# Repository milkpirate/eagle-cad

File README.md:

# eagle-cad
For this PCB development Eagle CAD v6.1.0 was heavily used. Could also contain code snippets.

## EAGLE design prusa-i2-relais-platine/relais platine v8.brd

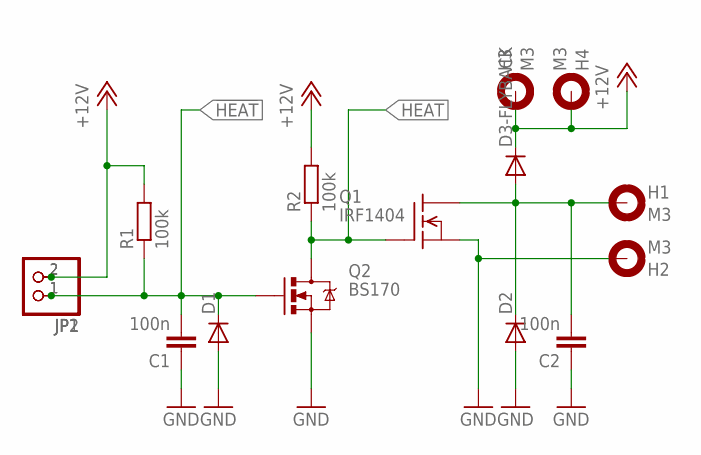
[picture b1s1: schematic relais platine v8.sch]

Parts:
C1, C2: 100n; C0805K
D1, D2, D3-FLYBACK: DIODE-MINIMELF; MINIMELF
H1, H2, H3, H4: M3; 3,0-PAD
JP1: PINHD-1X2; 1X02
JP2: PINHD-1X2/90; 1X02/90
Q1: IRF1404; TO220
Q2: BS170; SOT23-3
R1, R2: 100k; M0805

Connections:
!HEAT: C1.2, D1.C, JP1.1, JP2.1, Q2.1 (G), R1.1
+12V: D3-FLYBACK.C, H3.B3,0, H4.B3,0, JP1.2, JP2.2, R1.2, R2.2
GND: C1.1, C2.1, D1.A, D2.A, H2.B3,0, Q1.3 (S), Q2.2 (S)
HEAT: Q1.1 (G), Q2.3 (D), R2.1
HIGH: C2.2, D2.C, D3-FLYBACK.A, H1.B3,0, Q1.2 (D)

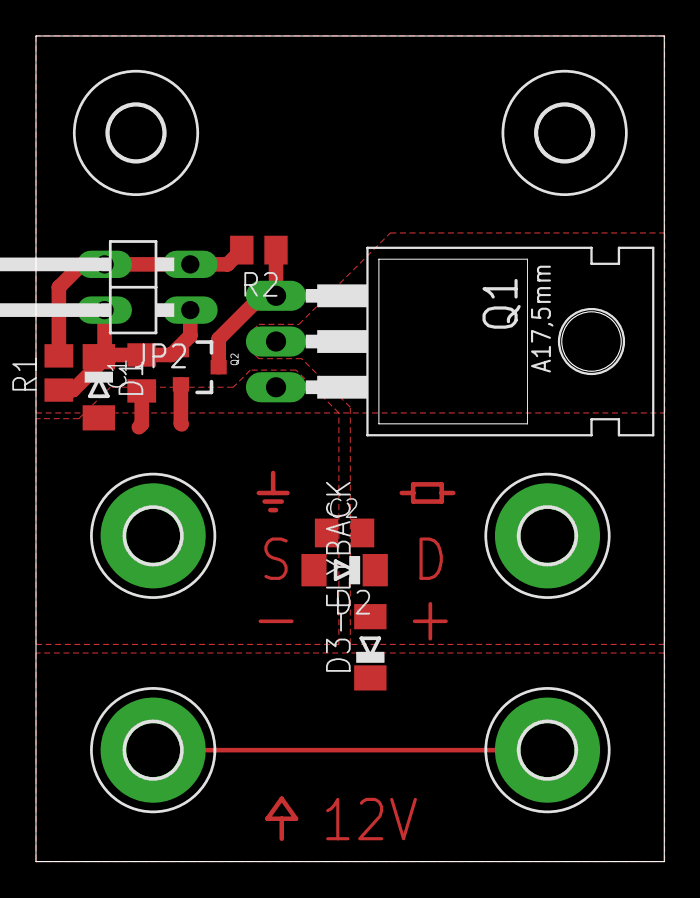
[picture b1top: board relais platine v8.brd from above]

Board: 2 copper layers, 34.9 x 45.9 mm, 17 parts (1 on the bottom side), 5 nets.

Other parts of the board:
U$1, U$2: 3,0

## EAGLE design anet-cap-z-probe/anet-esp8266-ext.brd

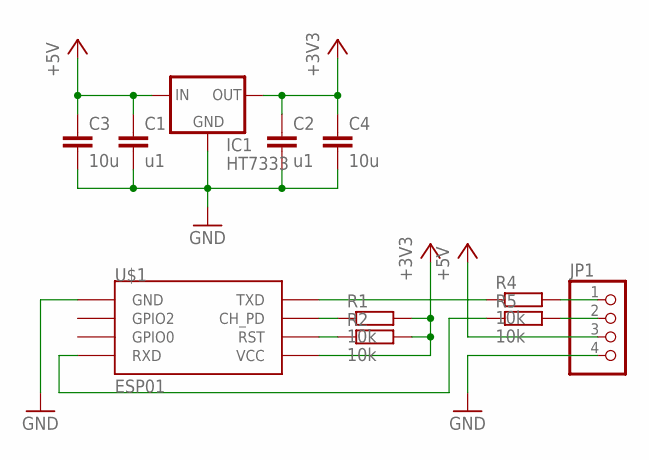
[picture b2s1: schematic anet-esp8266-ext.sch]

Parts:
C1: u1; C0805
C2: u1; C0805K
C3, C4: 10u; C0805K
IC1: HT7333; SOT-89
JP1: PINHD-1X4; 1X04
R1, R2, R5: 10k; M0805
R4: 10k; R0805
U$1: ESP01

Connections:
+3V3: C2.1, C4.1, IC1.1 (OUT), R1.2, R2.2, U$1.VCC
+5V: C1.1, C3.1, IC1.3 (IN), IC1.4 (IN), JP1.3
GND: C1.2, C2.2, C3.2, C4.2, IC1.2 (GND), JP1.4, U$1.GND
unnamed: R1.1, U$1.CH_PD
unnamed: JP1.1, R4.2
unnamed: JP1.2, R5.2
unnamed: R2.1, U$1.RST
RX: R5.1, U$1.RX (RXD)
TX: R4.1, U$1.TX (TXD)

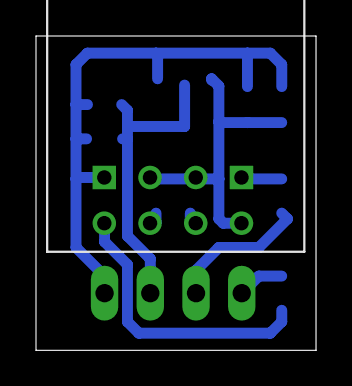
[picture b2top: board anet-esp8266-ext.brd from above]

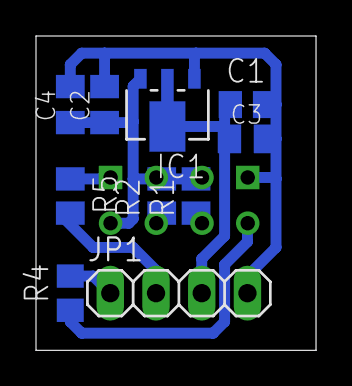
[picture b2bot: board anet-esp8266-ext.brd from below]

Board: 2 copper layers, 15.6 x 17.5 mm, 11 parts (10 on the bottom side), 9 nets.

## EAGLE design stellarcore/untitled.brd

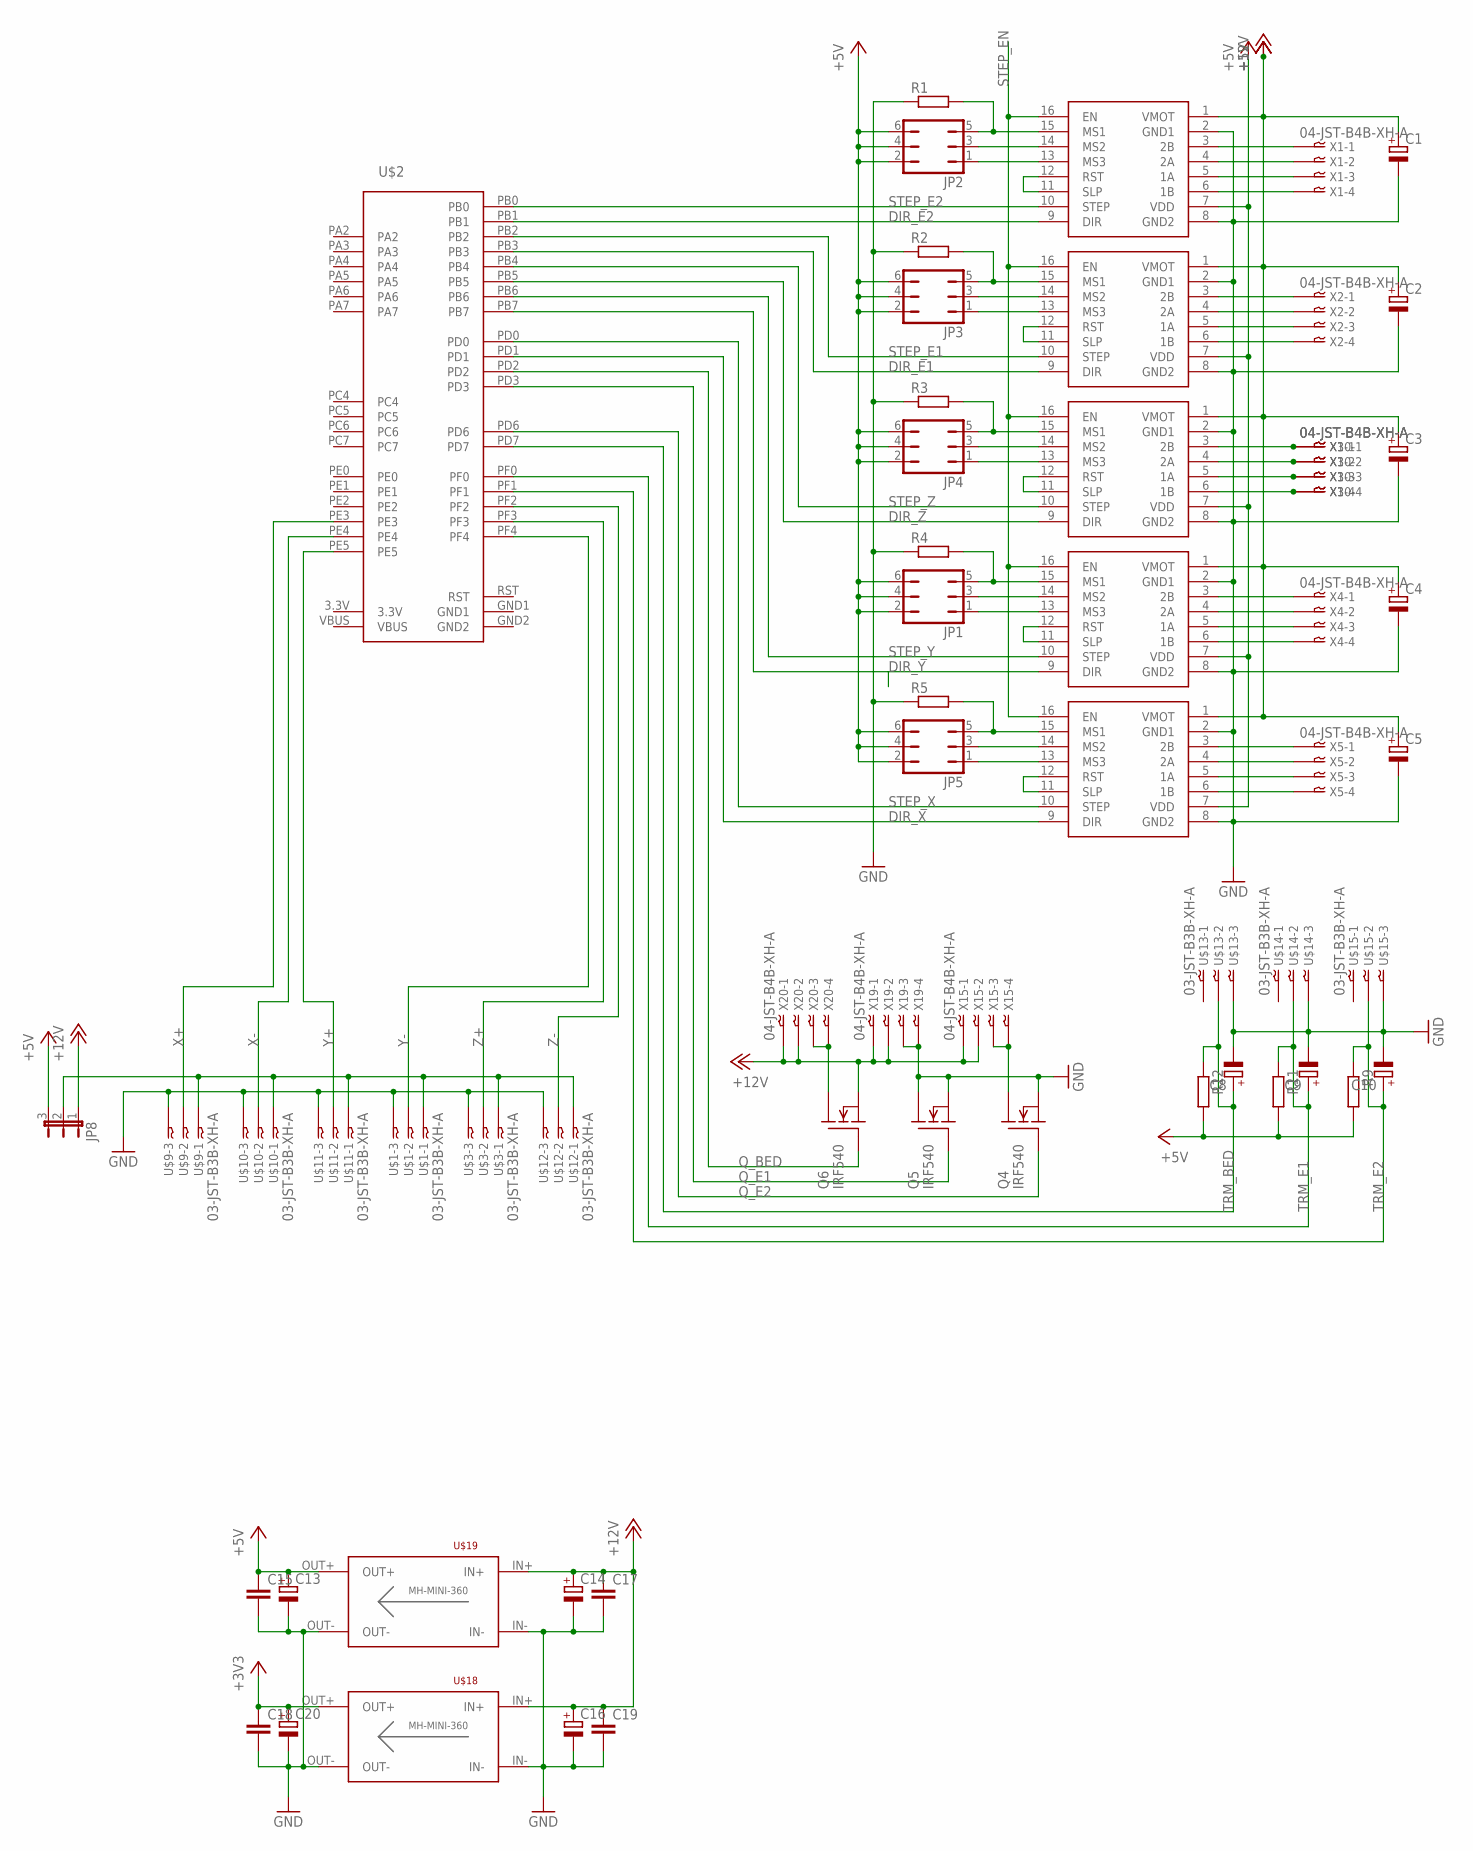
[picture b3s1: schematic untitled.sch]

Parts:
C1, C2, C3, C4, C5: CPOL-EUE2.5-7; E2,5-7
C8, C9, C10, C13, C14, C16, C20: CPOL-EUE2.5-5; E2,5-5
C15, C17, C18, C19: C-EU025-025X050; C025-025X050
JP1, JP2, JP3, JP4, JP5: JP3Q
JP8: JP2E; JP2
Q4, Q5, Q6: IRF540; TO220
R1, R2, R3, R4, R5, R9, R11, R12: R-EU_0204/7; 0204/7
U$1, U$3, U$9, U$10, U$11, U$12, U$13, U$14, U$15: 03-JST-B3B-XH-A; B3B-XH
U$2: STELLARIS-LAUNCHPADSTELLARIS-LAUNCHPAD; LAUNCHPAD-XL
U$4, U$5, U$6, U$7, U$8: POLOLUESTEPPERDRIVER; DIL16
U$18, U$19: DC-DC_CONV_MINISTD; DC-DC_CONV_MINI
X1, X2, X3, X4, X5, X10, X15, X19, X20: 04-JST-B4B-XH-A; B4B-XH

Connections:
3.3V: U$2.3.3V
+3V3: C18.1, C20.+, U$18.OUT+
+5V: C13.+, C15.1, JP1.2, JP1.4, JP1.6, JP2.2, JP2.4, JP2.6, JP3.2, JP3.4, JP3.6, JP4.2, JP4.4, JP4.6, JP5.2, JP5.4, JP5.6, JP8.3, R9.2, R11.2, R12.2, U$4.7 (VDD), U$5.7 (VDD), U$6.7 (VDD), U$7.7 (VDD), U$8.7 (VDD), U$19.OUT+
+12V: C1.+, C2.+, C3.+, C4.+, C5.+, C14.+, C16.+, C17.1, C19.1, JP8.1, Q6.3 (S), U$4.1 (VMOT), U$5.1 (VMOT), U$6.1 (VMOT), U$7.1 (VMOT), U$8.1 (VMOT), U$18.IN+, U$19.IN+, X15.P$1, X15.P$2, X19.P$1, X19.P$2, X20.P$1, X20.P$2
DIR_E1: U$2.PB3, U$7.9 (DIR)
DIR_E2: U$2.PB1, U$8.9 (DIR)
DIR_X: U$2.PD1, U$4.9 (DIR)
DIR_Y: U$5.9 (DIR)
DIR_Z: U$2.PB5, U$6.9 (DIR)
GND: C1.-, C2.-, C3.-, C4.-, C5.-, C8.-, C9.-, C10.-, C13.-, C14.-, C15.2, C16.-, C17.2, C18.2, C19.2, C20.-, Q4.3 (S), Q5.2 (D), Q5.3 (S), R1.1, R2.1, R3.1, R4.1, R5.1, U$1.P$3, U$3.P$3, U$4.2 (GND1), U$4.8 (GND2), U$5.2 (GND1), U$5.8 (GND2), U$6.2 (GND1), U$6.8 (GND2), U$7.2 (GND1), U$7.8 (GND2), U$8.2 (GND1), U$8.8 (GND2), U$9.P$3, U$10.P$3, U$11.P$3, U$12.P$3, U$13.P$3, U$14.P$3, U$15.P$3, U$18.IN-, U$18.OUT-, U$19.IN-, U$19.OUT-, X19.P$3, X19.P$4
GND2: U$2.GND2
unnamed: JP1.1, U$5.13 (MS3)
unnamed: JP1.3, U$5.14 (MS2)
unnamed: JP1.5, R4.2, U$5.15 (MS1)
unnamed: U$8.11 (SLP), U$8.12 (RST)
unnamed: U$7.11 (SLP), U$7.12 (RST)
unnamed: U$6.11 (SLP), U$6.12 (RST)
unnamed: U$5.11 (SLP), U$5.12 (RST)
unnamed: U$4.11 (SLP), U$4.12 (RST)
unnamed: JP2.1, U$8.13 (MS3)
unnamed: JP2.3, U$8.14 (MS2)
unnamed: JP2.5, R1.2, U$8.15 (MS1)
unnamed: JP3.1, U$7.13 (MS3)
unnamed: JP3.3, U$7.14 (MS2)
unnamed: JP3.5, R2.2, U$7.15 (MS1)
unnamed: JP4.1, U$6.13 (MS3)
unnamed: JP4.3, U$6.14 (MS2)
unnamed: JP4.5, R3.2, U$6.15 (MS1)
unnamed: JP5.1, U$4.13 (MS3)
unnamed: JP5.3, U$4.14 (MS2)
unnamed: JP5.5, R5.2, U$4.15 (MS1)
unnamed: U$8.3 (2B), X1.P$1
unnamed: U$8.4 (2A), X1.P$2
unnamed: U$8.5 (1A), X1.P$3
unnamed: U$8.6 (1B), X1.P$4
unnamed: U$7.3 (2B), X2.P$1
unnamed: U$7.4 (2A), X2.P$2
unnamed: U$7.5 (1A), X2.P$3
unnamed: U$7.6 (1B), X2.P$4
unnamed: U$6.3 (2B), X3.P$1, X10.P$1
unnamed: U$6.4 (2A), X3.P$2, X10.P$2
unnamed: U$6.5 (1A), X3.P$3, X10.P$3
unnamed: U$6.6 (1B), X3.P$4, X10.P$4
unnamed: U$5.3 (2B), X4.P$1
unnamed: U$5.4 (2A), X4.P$2
unnamed: U$5.5 (1A), X4.P$3
unnamed: U$5.6 (1B), X4.P$4
unnamed: U$4.3 (2B), X5.P$1
unnamed: U$4.4 (2A), X5.P$2
unnamed: U$4.5 (1A), X5.P$3
unnamed: U$4.6 (1B), X5.P$4
unnamed: JP8.2, U$1.P$1, U$3.P$1, U$9.P$1, U$10.P$1, U$11.P$1, U$12.P$1
unnamed: Q4.2 (D), X15.P$3, X15.P$4
unnamed: Q6.2 (D), X20.P$3, X20.P$4
Q_BED: Q6.1 (G), U$2.PD2
Q_E1: Q5.1 (G), U$2.PD3
Q_E2: Q4.1 (G), U$2.PD6
RST: U$2.RST
STEP_E1: U$2.PB2, U$7.10 (STEP)
STEP_E2: U$2.PB0, U$8.10 (STEP)
STEP_EN: U$4.16 (EN), U$5.16 (EN), U$6.16 (EN), U$7.16 (EN), U$8.16 (EN)
STEP_X: U$2.PD0, U$4.10 (STEP)
STEP_Y: U$2.PB6, U$5.10 (STEP)
STEP_Z: U$2.PB4, U$6.10 (STEP)
TRM_BED: C8.+, R12.1, U$2.PD7, U$13.P$2
TRM_E1: C9.+, R11.1, U$2.PF0, U$14.P$2
TRM_E2: C10.+, R9.1, U$2.PF1, U$15.P$2
VBUS: U$2.VBUS
X+: U$2.PE3, U$9.P$2
X-: U$2.PE4, U$10.P$2
Y+: U$2.PE5, U$11.P$2
Y-: U$1.P$2, U$2.PF4
Z+: U$2.PF3, U$3.P$2
Z-: U$2.PF2, U$12.P$2

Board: 2 copper layers, 59 parts (0 on the bottom side), 69 nets, no tracks yet.

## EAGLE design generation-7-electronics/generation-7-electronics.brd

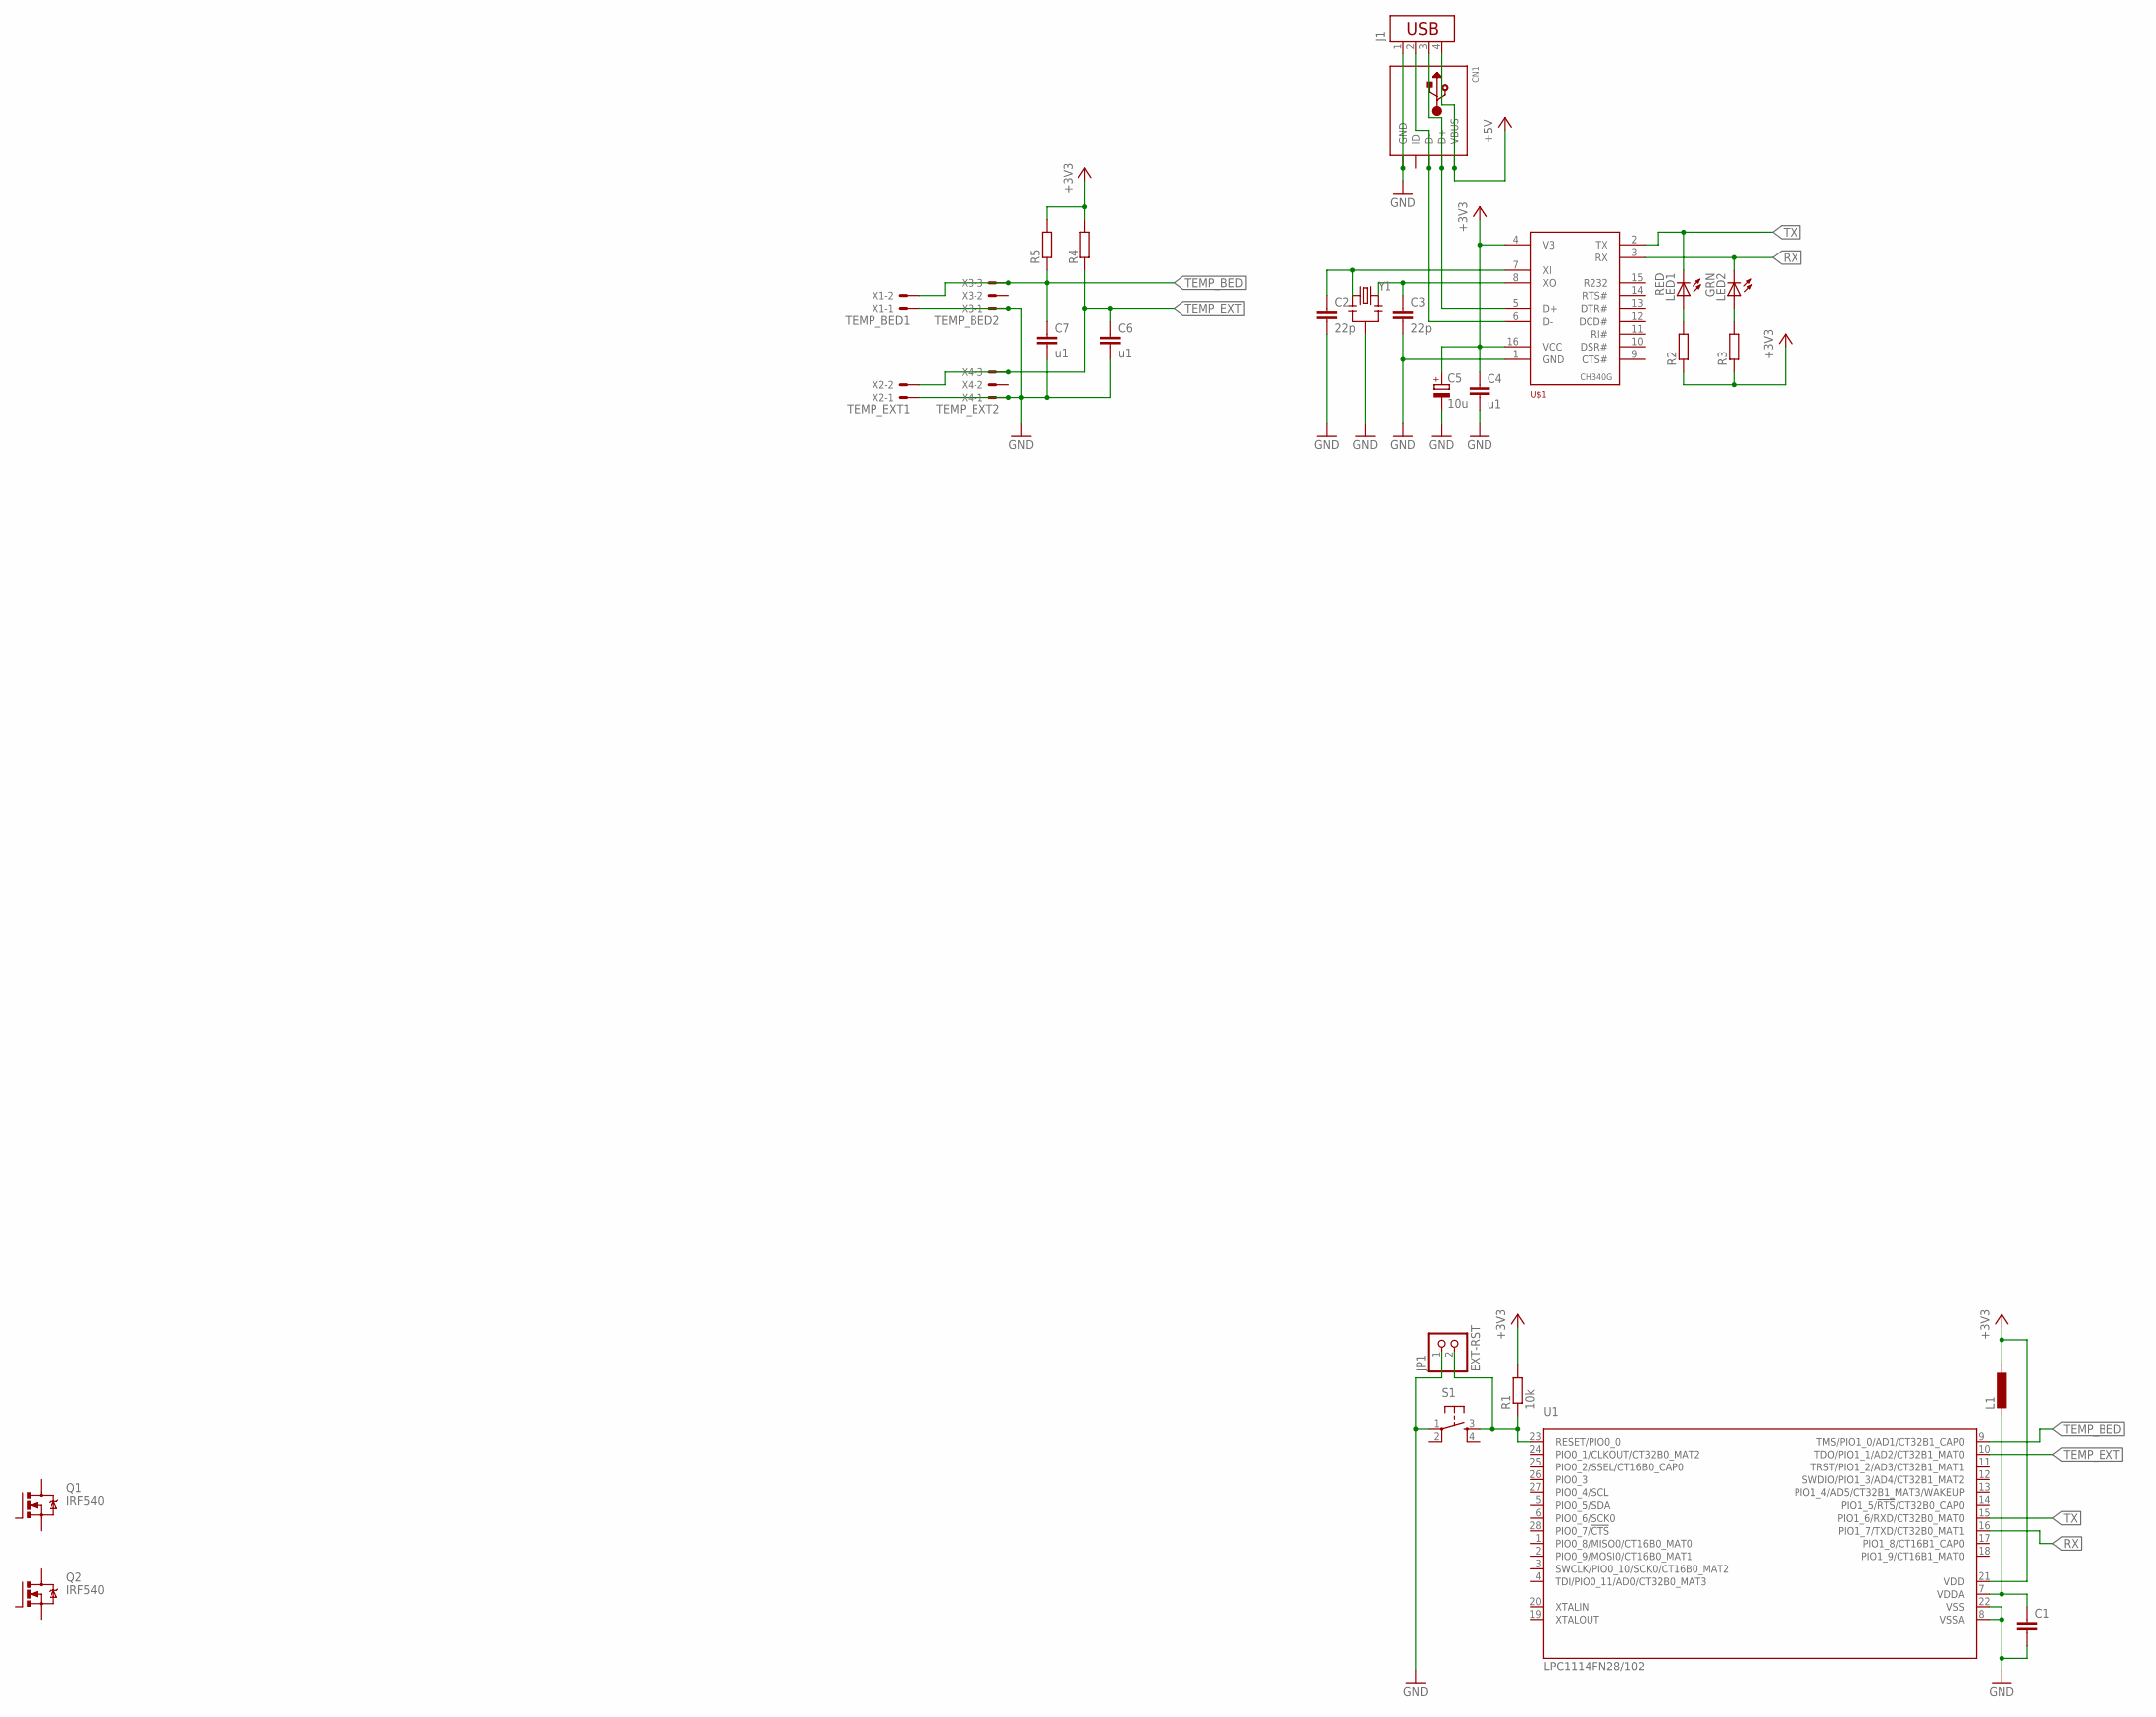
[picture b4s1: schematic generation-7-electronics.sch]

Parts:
C1: C-EU025-025X050; C025-025X050
C2, C3: 22p; C025-025X050
C4, C6, C7: u1; C025-025X050
C5: 10u; E2,5-6
CN1: USBTHM; USB-MINIB-THM
J1: CON-USB-B; USB-B
JP1: EXT-RST; 1X02
L1: L-EU0207/2V; 0207/2V
LED1: RED; LED3MM
LED2: GRN; LED3MM
Q1, Q2: IRF540; TO220BV
R1: 10k; 0204/7
R2, R3, R4, R5: R-EU_0204/7; 0204/7
S1: TAC_SWITCHPTH; TACTILE-PTH
U1: LPC1114FN28/102; SOT117
U$1: CH340G; SO16
X1: TEMP_BED1; JST-XH-02-PACKAGE-LONG-PAD
X2: TEMP_EXT1; JST-XH-02-PACKAGE-LONG-PAD
X3: TEMP_BED2; JST-XH-03-PACKAGE-LONG-PAD
X4: TEMP_EXT2; JST-XH-03-PACKAGE-LONG-PAD
Y1: RESONATORPTH; RESONATOR-PTH

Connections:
+3V3: C4.1, C5.+, L1.1, R1.2, R2.1, R3.1, R4.2, R5.2, U1.21 (VDD), U$1.4 (V3), U$1.16 (VCC)
+5V: CN1.VBUS, J1.4
GND: C1.2, C2.2, C3.2, C4.2, C5.-, C6.2, C7.2, CN1.GND, J1.1, JP1.1, S1.1, U1.8 (VSSA), U1.22 (VSS), U$1.1 (GND), X1.1, X2.1, X3.1, X4.1, Y1.2
unnamed: C1.1, L1.2, U1.7 (VDDA)
unnamed: JP1.2, R1.1, S1.3, U1.23 (RESET/PIO0_0)
unnamed: CN1.D-, J1.2, U$1.6 (D-)
unnamed: LED1.A, R2.2
unnamed: C2.1, U$1.7 (XI), Y1.1
unnamed: C3.1, U$1.8 (XO), Y1.3
unnamed: LED2.A, R3.2
unnamed: CN1.D+, J1.3, U$1.5 (D+)
RX: LED2.K (C), U1.16 (PIO1_7/TXD/CT32B0_MAT1), U$1.3 (RX)
TEMP_BED: C7.1, R5.1, U1.9 (TMS/PIO1_0/AD1/CT32B1_CAP0), X1.2, X3.3
TEMP_EXT: C6.1, R4.1, U1.10 (TDO/PIO1_1/AD2/CT32B1_MAT0), X2.2, X4.3
TX: LED1.K (C), U1.15 (PIO1_6/RXD/CT32B0_MAT0), U$1.2 (TX)

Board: 2 copper layers, 28 parts (0 on the bottom side), 15 nets, no tracks yet.

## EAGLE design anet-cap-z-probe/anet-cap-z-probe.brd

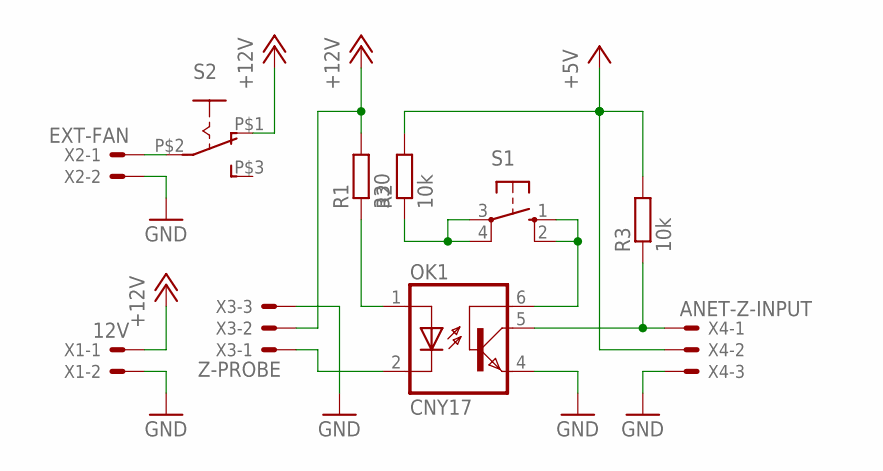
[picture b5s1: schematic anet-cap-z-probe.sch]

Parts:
OK1: CNY17; DIL06
R1: 330; R0805
R2, R3: 10k; R0805
S1: 10-XX; B3F-10XX
S2: EG1218THIN; THIN
X1: 12V; JST-XH-02-PACKAGE-LONG-PAD
X2: EXT-FAN; JST-XH-02-PACKAGE-LONG-PAD
X3: Z-PROBE; JST-XH-03-PACKAGE-LONG-PAD
X4: ANET-Z-INPUT; JST-XH-03-PACKAGE-LONG-PAD

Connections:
+5V: R2.2, R3.2, X4.2
+12V: R1.2, S2.P$1 (O), X1.1, X3.2
GND: OK1.4 (EMI), X1.2, X2.2, X3.3, X4.3
unnamed: S2.P$2, X2.1
unnamed: OK1.5 (COL), R3.1, X4.1
unnamed: R2.1, S1.3, S1.4 (P1)
unnamed: OK1.6 (BAS), S1.1 (S), S1.2 (S1)
unnamed: OK1.1 (A), R1.1
unnamed: OK1.2 (C), X3.1

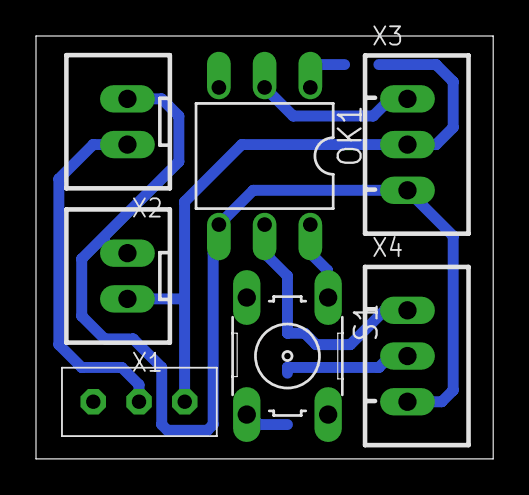
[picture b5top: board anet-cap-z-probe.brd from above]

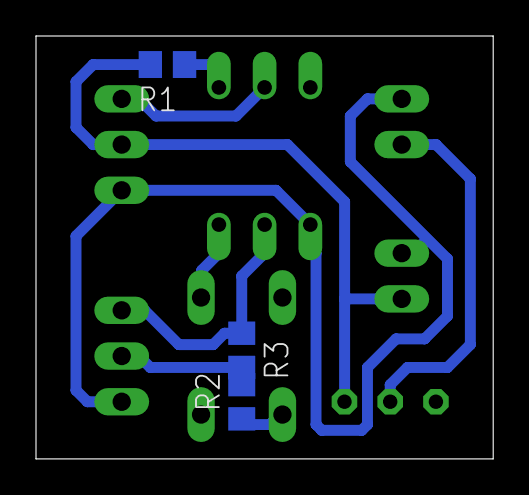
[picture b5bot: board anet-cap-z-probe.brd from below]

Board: 2 copper layers, 25.4 x 23.5 mm, 10 parts (3 on the bottom side), 9 nets.

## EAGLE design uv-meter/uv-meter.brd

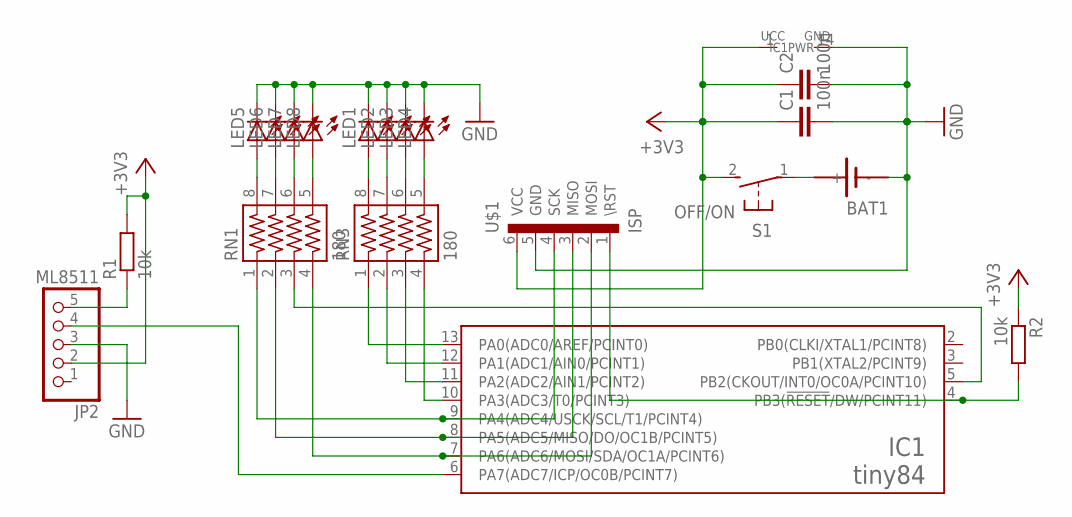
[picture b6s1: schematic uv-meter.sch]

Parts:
BAT1: SN2032
C1, C2: 100n; C0805K
IC1: tiny84; SOIC14
JP2: ML8511; 1X05
LED1, LED2, LED3, LED4, LED5, LED6, LED7, LED8: LEDSML0805; SML0805
R1, R2: 10k; M0805
RN1, RN3: 180; 744-8NS
S1: OFF/ON; DTS-3
U$1: ISP; POGOPROG-CONN

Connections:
+3V3: C1.1, C2.1, IC1.1 (UCC), JP2.2, R1.2, R2.1, S1.2, U$1.6 (VCC)
GND: BAT1.-, C1.2, C2.2, IC1.14 (GND), JP2.3, LED1.C, LED2.C, LED3.C, LED4.C, LED5.C, LED6.C, LED7.C, LED8.C, U$1.5 (GND)
unnamed: LED5.A, RN1.8
unnamed: JP2.5, R1.1
unnamed: LED6.A, RN1.7
unnamed: LED7.A, RN1.6
unnamed: LED8.A, RN1.5
unnamed: LED1.A, RN3.8
unnamed: LED2.A, RN3.7
unnamed: BAT1.+, S1.1
unnamed: LED3.A, RN3.6
unnamed: LED4.A, RN3.5
unnamed: IC1.10 (PA3(ADC3/T0/PCINT3)), RN3.4
unnamed: IC1.11 (PA2(ADC2/AIN1/PCINT2)), RN3.3
unnamed: IC1.12 (PA1(ADC1/AIN0/PCINT1)), RN3.2
unnamed: IC1.5 (PB2(CKOUT/INT0/OC0A/PCINT10)), RN1.3
unnamed: IC1.13 (PA0(ADC0/AREF/PCINT0)), RN3.1
unnamed: IC1.7 (PA6(ADC6/MOSI/SDA/OC1A/PCINT6)), RN1.4, U$1.2 (MOSI)
unnamed: IC1.8 (PA5(ADC5/MISO/DO/OC1B/PCINT5)), RN1.2, U$1.3 (MISO)
unnamed: IC1.9 (PA4(ADC4/USCK/SCL/T1/PCINT4)), RN1.1, U$1.4 (SCK)
unnamed: IC1.6 (PA7(ADC7/ICP/OC0B/PCINT7)), JP2.4
unnamed: IC1.4 (PB3(!RESET!/DW/PCINT11)), R2.2, U$1.1 (\RST)

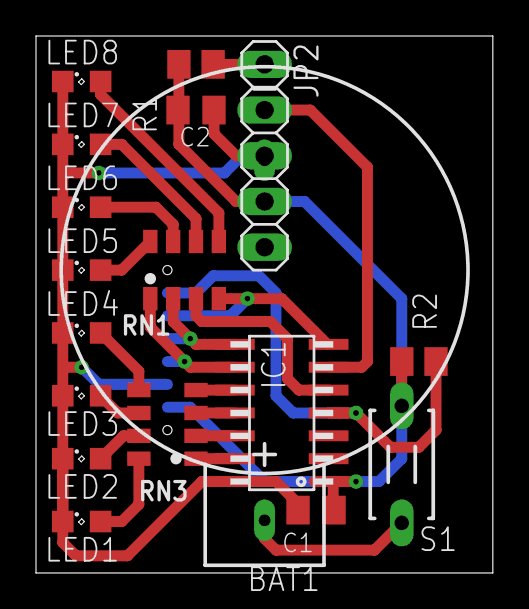
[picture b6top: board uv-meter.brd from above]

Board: 2 copper layers, 25.4 x 29.8 mm, 19 parts (1 on the bottom side), 22 nets.

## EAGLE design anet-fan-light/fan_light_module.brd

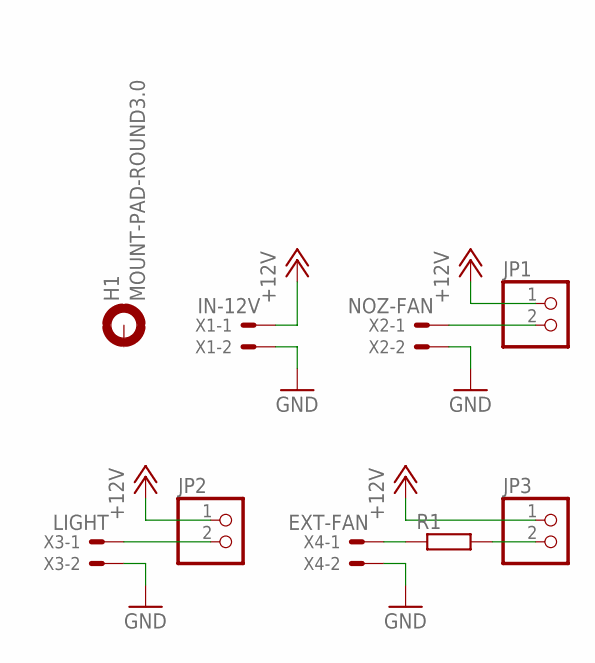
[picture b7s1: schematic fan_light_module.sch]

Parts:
H1: MOUNT-PAD-ROUND3.0; 3,0-PAD
JP1, JP2, JP3: PINHD-1X2; 1X02
R1: R-EU_0204/7; 0204/7
X1: IN-12V; JST-XH-02-PACKAGE-LONG-PAD
X2: NOZ-FAN; JST-XH-02-PACKAGE-LONG-PAD
X3: LIGHT; JST-XH-02-PACKAGE-LONG-PAD
X4: EXT-FAN; JST-XH-02-PACKAGE-LONG-PAD

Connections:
+12V: JP1.1, JP2.1, JP3.1, X1.1
GND: X1.2, X2.2, X3.2, X4.2
unnamed: JP1.2, X2.1
unnamed: JP2.2, X3.1
unnamed: R1.1, X4.1
unnamed: JP3.2, R1.2

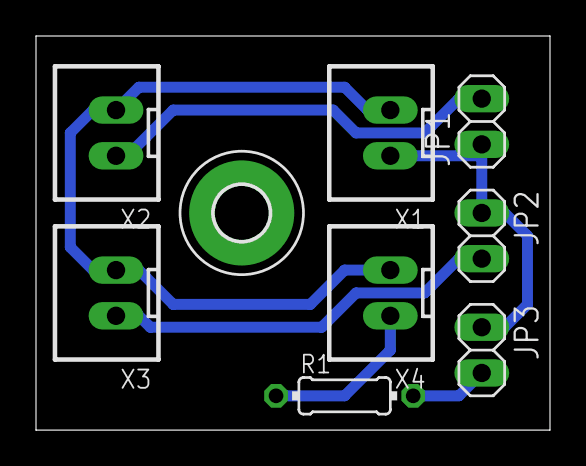
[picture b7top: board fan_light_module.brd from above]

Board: 2 copper layers, 28.6 x 21.9 mm, 9 parts (0 on the bottom side), 6 nets.

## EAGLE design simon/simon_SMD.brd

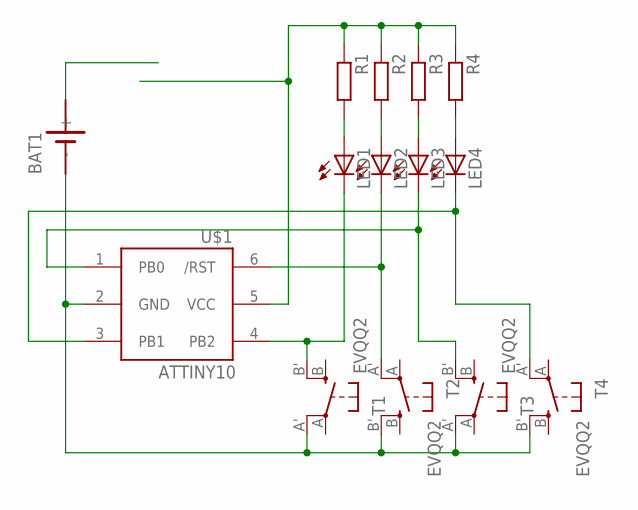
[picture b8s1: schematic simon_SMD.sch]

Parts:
BAT1: SN2032
LED1, LED2, LED3, LED4: LEDCHIP-LED0805; CHIP-LED0805
R1, R2, R3, R4: R-EU_M0805; M0805
T1, T2, T3, T4: EVQQ2; EVQ-Q2
U$1: ATTINY10; SOT23-6

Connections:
unnamed: LED4.A, R4.2
unnamed: LED3.A, R3.2
unnamed: LED2.A, R2.2
unnamed: LED1.A, R1.2
unnamed: LED2.C, T2.A' (P1), U$1.6 (/RST)
unnamed: R1.1, R2.1, R3.1, R4.1, U$1.5 (VCC)
unnamed: LED1.C, T1.B' (S1), U$1.4 (PB2)
unnamed: LED3.C, T3.B' (S1), U$1.1 (PB0)
unnamed: LED4.C, T4.A' (P1), U$1.3 (PB1)
unnamed: BAT1.-, T1.A' (P1), T2.B' (S1), T3.A' (P1), T4.B' (S1), U$1.2 (GND)

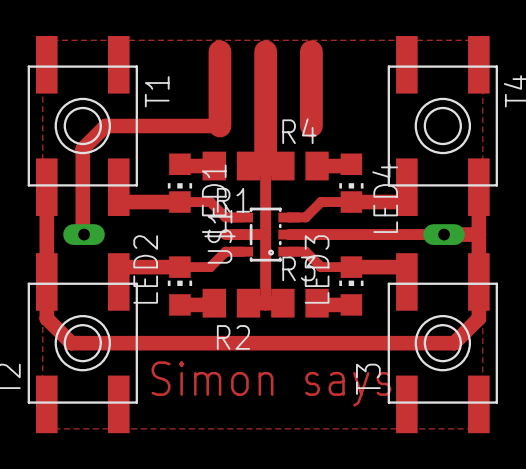
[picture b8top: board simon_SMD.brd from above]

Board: 2 copper layers, 14 parts (1 on the bottom side), 10 nets.

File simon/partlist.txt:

Partlist

Exported from simon_SMD.sch at 21.05.2013 23:48:45

EAGLE Version 6.1.0 Copyright (c) 1988-2012 CadSoft

Assembly variant: 

Part     Value          Device          Package      Library      Sheet

BAT1                    SN2032          SN2032       sn2032       1
LED1                    LEDCHIP-LED0805 CHIP-LED0805 led          1
LED2                    LEDCHIP-LED0805 CHIP-LED0805 led          1
LED3                    LEDCHIP-LED0805 CHIP-LED0805 led          1
LED4                    LEDCHIP-LED0805 CHIP-LED0805 led          1
R1                      R-EU_M0805      M0805        rcl          1
R2                      R-EU_M0805      M0805        rcl          1
R3                      R-EU_M0805      M0805        rcl          1
R4                      R-EU_M0805      M0805        rcl          1
T1       EVQQ2          EVQQ2           EVQ-Q2       adafruit_t10 1
T2       EVQQ2          EVQQ2           EVQ-Q2       adafruit_t10 1
T3       EVQQ2          EVQQ2           EVQ-Q2       adafruit_t10 1
T4       EVQQ2          EVQQ2           EVQ-Q2       adafruit_t10 1
U$1      ATTINY10       ATTINY10        SOT23-6      adafruit_t10 1

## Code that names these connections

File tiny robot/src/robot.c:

/* -----------------------------------------------------------------------
 * Title:    tiny braitenberg
 * Author:   Alexander Weber <alex@tinkerlog.com>
 *           http://tinkerlog.com
 * Date:     24.07.2009
 * Hardware: ATtiny25v, ATtiny45 or 85 will work as well.
 *
 * If using a lipo-cell, never get under 2.5 V.
 */

#include <avr/io.h>
#include <avr/interrupt.h>
#include <util/delay.h>
#include <stdlib.h>

#define min(a,b) ((a)<(b)?(a):(b))
#define max(a,b) ((a)>(b)?(a):(b))
#define saturation(x,a,b) min(max(x,a),b)

#define LED_BIT PB0
#define LEFT_MOTOR_BIT PB1
#define RIGHT_MOTOR_BIT PB2
#define LEFT_SENSOR_BIT PB3
#define RIGHT_SENSOR_BIT PB4

#define LEFT_OFFSET 10
#define RIGHT_OFFSET 0

static int16_t left_sensor = 0;
static int16_t right_sensor = 0;
static volatile uint8_t left_motor = 0;
static volatile uint8_t right_motor = 0;
static volatile uint8_t act_left_motor = 0;
static volatile uint8_t act_right_motor = 0;
static uint8_t count = 0;


/* -----------------------------------------------------
 * ADC interrupt
 * TODO: use ADC in free running mode
 */
SIGNAL(ADC_vect) {
  // act_light = ADCH;        // read only 8-bit
}


/* -----------------------------------------------------
 * Timer0 overflow interrupt
 * F_CPU 8.000.000 Hz 
 * -> prescaler 0, overrun 256 -> 31.250 Hz 
 * -> 256 steps -> 122 Hz
 *
 */
SIGNAL(TIM0_OVF_vect) {	
  // every 256th step take over new values
  if (++count == 0) {    
    act_left_motor = left_motor + LEFT_OFFSET;
    act_right_motor = right_motor + RIGHT_OFFSET;
    if (act_left_motor > 40) {
      PORTB |= (1 << LEFT_MOTOR_BIT);      
    }
    if (act_right_motor > 40) {
      PORTB |= (1 << RIGHT_MOTOR_BIT);
    }
  }
  if (count == act_left_motor) {
    PORTB &= ~(1 << LEFT_MOTOR_BIT);
  }
  if (count == act_right_motor) {
    PORTB &= ~(1 << RIGHT_MOTOR_BIT);
  }
}



/*
 * get_adc
 * Return the 8 bit value of the selected adc channel.
 */
uint16_t get_adc(uint8_t channel) {

  // ADC setup
  ADCSRA = 
    (1 << ADEN) |                   // enable ADC
    (1 << ADPS1) | (1 << ADPS0);    // set prescaler to 8	
		
  // select channel
  ADMUX = channel;
	
  // select reference voltage
  // ADMUX |= (1 << REFS0);	   // use internal reference

  // warm up the ADC, discard the first conversion
  ADCSRA |= (1 << ADSC);
  while (ADCSRA & (1 << ADSC)); 

  ADCSRA |= (1 << ADSC);           // start single conversion
  while (ADCSRA & (1 << ADSC));    // wait until conversion is done
		
  return ADCW;
}


uint16_t scale_down(uint16_t v) {
  v = max(300, v);
  v -= 300;
  // v /= 6;
  v >>= 2;
  v = min(120, v);
  return v;
}


int main(void) {	
	
  uint8_t i = 0;
	
  // eneable pins as output
  DDRB |= 
    (1 << LED_BIT) |
    (1 << LEFT_MOTOR_BIT) |
    (1 << RIGHT_MOTOR_BIT);

  // timer 0 setup, prescaler none
  TCCR0B |= (0 << CS02) | (0 << CS01) | (1 << CS00);

  // enable timer 0 interrupt
  TIMSK |= (1 << TOIE0);	
  // TIMSK0 |= (1 << TOIE0);	

  // enable all interrupts
  sei();


  // intro, blink led
  for (i = 0; i < 5; i++) {
    PORTB |= (1 << LED_BIT);	
    _delay_ms(100);
    PORTB &= ~(1 << LED_BIT);
    _delay_ms(100);
  }

  _delay_ms(5000);

  while (1) {

    /* motor starts with 5 
    for (i = 0; i < 15; i++) {
      right_motor = i * 10;
      left_motor = i * 10;
      _delay_ms(5000);
      right_motor = 0;
      left_motor = 0;
      PORTB |= (1 << LED_BIT);	
      _delay_ms(500);
      PORTB &= ~(1 << LED_BIT);
    }
    */

    // sensor reads from ~100 to 800
    left_sensor = get_adc(2);
    right_sensor = get_adc(3);

    // scale down
    left_sensor = scale_down(left_sensor);
    right_sensor = scale_down(right_sensor);

    // give some visual feedback
    if (abs(left_sensor - right_sensor) < 10) {
      PORTB |= (1 << LED_BIT);
    }
    else {
      PORTB &= ~(1 << LED_BIT);
    }

    // aggression
    right_motor = left_sensor;
    left_motor = right_sensor;

    // love
    // right_motor = 120 - right_sensor;
    // left_motor = 120 - left_sensor;

    // fear
    // right_motor = right_sensor;
    // left_motor = left_sensor;

    _delay_ms(10);
  }
  return 0;
}

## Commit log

2017-03-16 3d printing adons
2017-05-05 new projects

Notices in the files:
parts and their libraries:
SparkFun-FreqCtrl: Licensing: CC v3.0 Share-Alike You are welcome to use this library for commercial purposes.
SparkFun-Electromechanical: Licensing: Creative Commons ShareAlike 4.0 International - https://creativecommons.org/licenses/by-sa/4.0
resistor-array: Copyright (C) 2008, Bob Starr
